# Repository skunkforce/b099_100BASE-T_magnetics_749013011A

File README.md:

# edgy_board number b099
This design is part of the [edgy board project](https://github.com/skunkforce/edgy_boards).

# getting started
This repository uses submodules. After cloning use the command 

```$ git submodule update --init --recursive```

to pull the submodules before opening the project with kicad. 

# Tests
Tests can be found in [TESTS.md](TESTS.md)

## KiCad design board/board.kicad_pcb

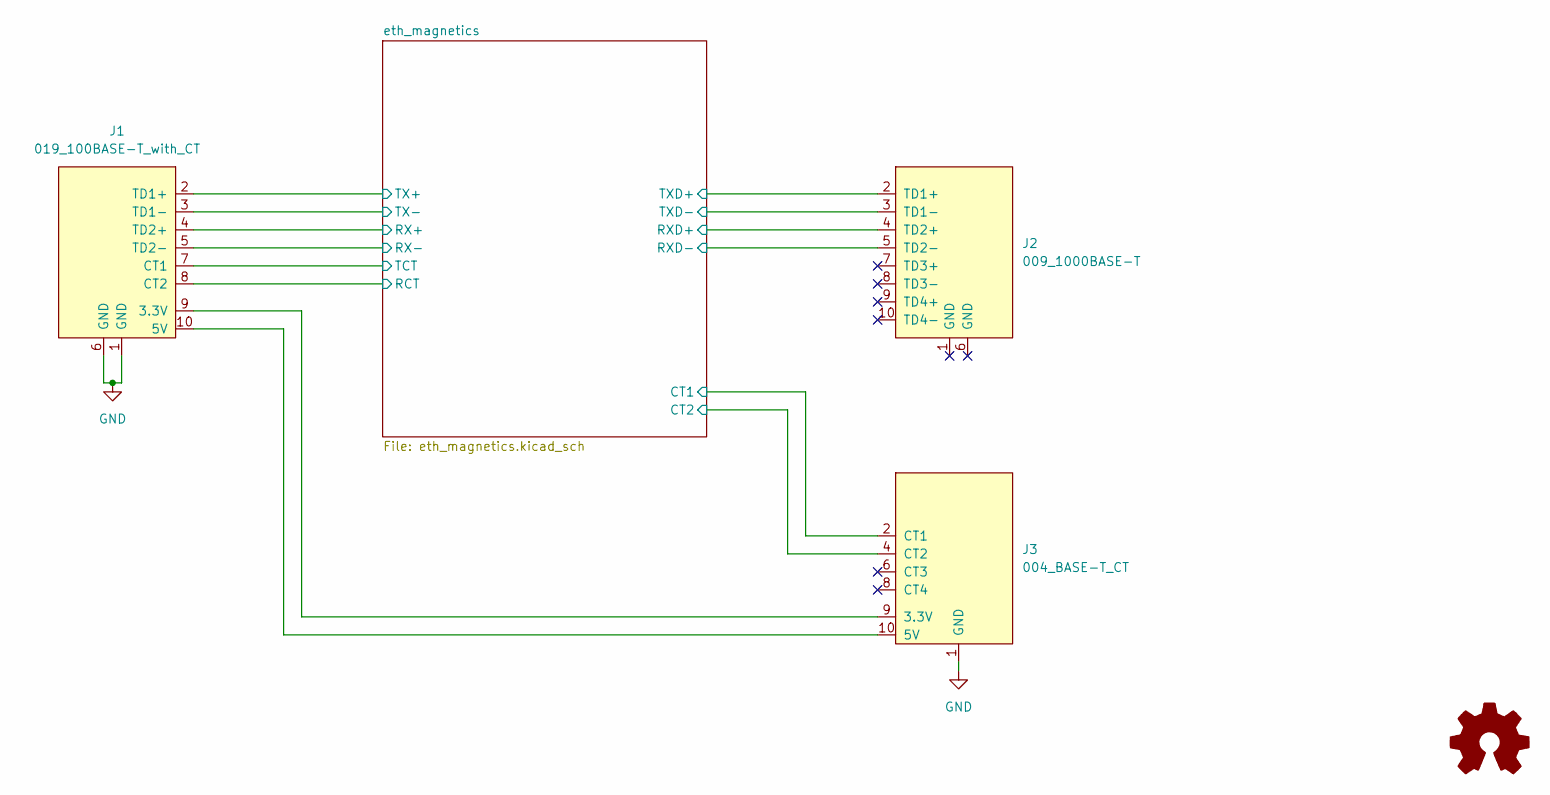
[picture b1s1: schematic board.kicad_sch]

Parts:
J1: 019_100BASE-T_with_CT; on_edge_2x05_device
J2: 009_1000BASE-T; on_edge_2x05_host
J3: 004_BASE-T_CT; on_edge_2x05_host
LOGO1: Logo_Open_Hardware_Small; OSHW-Symbol_6.7x6mm_SilkScreen

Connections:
/eth_magnetics/CT1: J3.2 (CT1); also elsewhere on the board
/eth_magnetics/CT2: J3.4 (CT2); also elsewhere on the board
/eth_magnetics/RCT: J1.8 (CT2); also elsewhere on the board
/eth_magnetics/RX+: J1.4 (TD2+); also elsewhere on the board
/eth_magnetics/RX-: J1.5 (TD2-); also elsewhere on the board
/eth_magnetics/RXD+: J2.4 (TD2+); also elsewhere on the board
/eth_magnetics/RXD-: J2.5 (TD2-); also elsewhere on the board
/eth_magnetics/TCT: J1.7 (CT1); also elsewhere on the board
/eth_magnetics/TX+: J1.2 (TD1+); also elsewhere on the board
/eth_magnetics/TX-: J1.3 (TD1-); also elsewhere on the board
/eth_magnetics/TXD+: J2.2 (TD1+); also elsewhere on the board
/eth_magnetics/TXD-: J2.3 (TD1-); also elsewhere on the board
GND: J1.1 (GND), J1.6 (GND), J3.1 (GND)
unnamed: J1.9 (3.3V), J3.9 (3.3V)
unnamed: J1.10 (5V), J3.10 (5V)

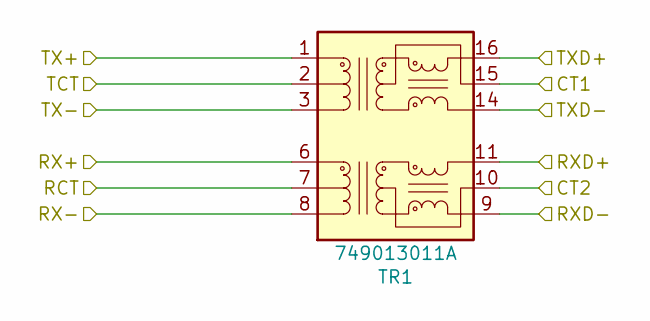
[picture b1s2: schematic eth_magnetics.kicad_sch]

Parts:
TR1: 749013011A; Digi-Key_PN 732-7063-1-ND

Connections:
/eth_magnetics/CT1: TR1.15 (C_TX); also elsewhere on the board
/eth_magnetics/CT2: TR1.10 (C_RX); also elsewhere on the board
/eth_magnetics/RCT: TR1.7 (C_RD); also elsewhere on the board
/eth_magnetics/RX+: TR1.6 (RD+); also elsewhere on the board
/eth_magnetics/RX-: TR1.8 (RD-); also elsewhere on the board
/eth_magnetics/RXD+: TR1.11 (RX+); also elsewhere on the board
/eth_magnetics/RXD-: TR1.9 (RX-); also elsewhere on the board
/eth_magnetics/TCT: TR1.2 (C_TD); also elsewhere on the board
/eth_magnetics/TX+: TR1.1 (TD+); also elsewhere on the board
/eth_magnetics/TX-: TR1.3 (TD-); also elsewhere on the board
/eth_magnetics/TXD+: TR1.16 (TX+); also elsewhere on the board
/eth_magnetics/TXD-: TR1.14 (TX-); also elsewhere on the board

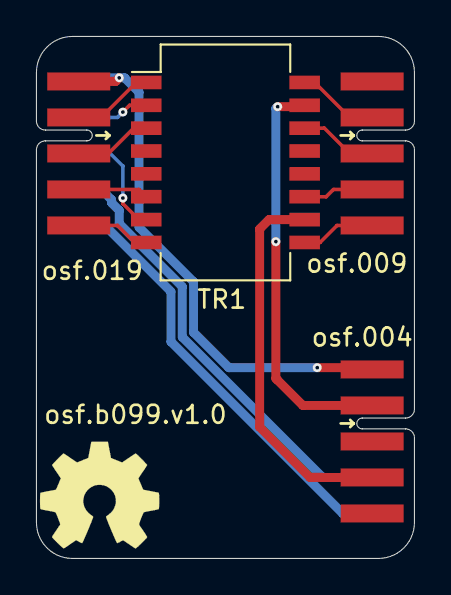
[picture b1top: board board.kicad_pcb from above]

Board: 2 copper layers, 21.0 x 29.0 mm, 5 parts (0 on the bottom side), 15 nets.

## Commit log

2023-02-23 initial
2023-03-04 updated to use put_on_edge v1.0 connectors
